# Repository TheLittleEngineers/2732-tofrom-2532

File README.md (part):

# 2732-tofrom-2532 - GCC-ECS-0001.1 - 2732/2532 E.P.R.O.M. Socket Converter

<!DOCTYPE html>
<html>
<head>

<meta name="Author" content="Robert &quot;The R.A.T.&quot; Allen Turner">
<meta name="GENERATOR" content="Tandy Radio Shack TRS-80 Color Computer 3">
<meta name="ProgId" content="TeleWriter-128.by.Bob.Van.der.Poel.for.Cognitec">
<meta http-equiv="Content-Type" content="text/html; charset=UTF-8">
<meta http-equiv="Content-Language" content="en-us">
<meta name="viewport" content="width=device-width, initial-scale=1">
<!--
<!meta http-equiv="Content-Type" content="text/html; charset=windows-1252">
This HTML is a veritable train wreck, however, it seems to get the job done on 24 September 2020 and beyond
-->

</head>

<body style="background-color:WhiteSmoke;">

<!-- Top Row -->
<div align="center">
  
<center>
  
<p align="center"><font size="6">

This page created: April 7, 2019, last updated: September 24, 2020.<br>
2732-tofrom-2532 - GCC-ECS-0001.1<br></font>
<font size="5"><em>2732/2532 E.P.R.O.M. Socket Converter</em><br></font><font size="4">A Project By <a href="http://www.TheLittleEngineers.org/" target="_blank">
The Little Engineers</a>.<br>Copyright &copy;2019, by:<br>
Robert "The R.A.T." Allen Turner<br>
<a href="http://www.TheLittleEngineers.org/" target="_blank">http://www.TheLittleEngineers.org/</a><br>
<a href="mailto:TheLittleEngineers@outlook.com">TheLittleEngineers@outlook.com</a><br>
<a href="mailto:OurLittleEngineers@gMail.com">OurLittleEngineers@gMail.com</a><br></div>
<div align="justify">
<p align="justify"><b>(Deprecated - See below for 
<a href="https://github.com/TheLittleEngineers/2732-to-2532" target="_blank">link</a> to the new version).</b>
</p>
This product is intended to allow a 2732 EPROM to be placed into a 2532 EPROM socket or a 2532 EPROM to be placed into a 2732 EPROM socket. The original product seems to have been placed on
<a href="https://github.com/TheLittleEngineers/" target="_blank">GitHub</a> at this url: 
<a href="https://github.com/ricardoquesada/2732-to-2532" target="_blank">https://github.com/ricardoquesada/2732-to-2532</a>. Being somewhat involved in the original creation of the product, I decided not to fork that repository for this new, slightly improved version, but rather chose to create a new repository. The product is now licensed under a 
<a href="https://creativecommons.org/licenses/by-sa/4.0/" target="_blank">Creative Commons Attribution-ShareAlike 4.0 International</a> (<a href="https://creativecommons.org/licenses/by-sa/4.0/legalcode" target="_blank">CC BY-SA 4.0</a>) License 
<i>IN MEMORY OF MY FATHER, ROBERT EMBRY TURNER</i>.</p>
<hr align="justify">
<p align="center">This version of the product has been shared to 
<a href="https://oshpark.com/shared_projects/nMURuBKv" target="_blank">OSHPark</a>: 
<a href="https://oshpark.com/shared_projects/nMURuBKv" target="_blank">https://oshpark.com/shared_projects/nMURuBKv</a>
<br>
&nbsp;</p>
<p align="center"><b>2732 <--> 2532 Adapter Board: GCC-ECS-0001.1,<br>2532 <===> 2732 Socket Converter,<br>Original Part Number: GCC-ECS-0001.0,<br>Copyright (C) 04 May 2010,<br<By: "Little" John Eric Turner and "Big" John Robert Turner,<br>All Rights Reserved.<br>
<a href="http://www.GIMEchip.com/" target="_blank">http://www.GIMEchip.com/</a><br>Updated Part Number: GCC-ECS-0001.1,<br>By: "Uncle" Robert "The R.A.T." Allen Turner at the behest of "Little" and "Big" John,<br>Copyright (C) 09 April 2019,<br>Released under a 
<a href="https://creativecommons.org/licenses/by-sa/4.0/" target="_blank">Creative Commons Attribution-ShareAlike 4.0 International</a> (<a href="https://creativecommons.org/licenses/by-sa/4.0/legalcode" target="_blank">CC BY-SA 4.0</a>) License<br>IN MEMORY OF MY FATHER: ROBERT EMBRY TURNER. I LOVE AND MISS YOU DADDY! REST IN PEACE.</b></p>
      <br<By: "Little" John Eric Turner and "Big" John Robert Turner,<br>
<hr align="justify">
<p align="justify">This product is intended to allow a 2732 EPROM to be placed into a 2532 EPROM socket or a 2532 EPROM to be placed into a 2732 EPROM socket. Fitting I.C. pins for IC1 and a socket for IC2 allows a 2732 to be plugged into a 2532 socket, whilst fitting I.C. pins for IC2 and a socket for IC1 allows a 2532 to be plugged into a 2732 socket. It is recommended that "round pin headers" be used for the I.C. pins as they will plug directly into standard I.C. sockets without stressing them which would result in potential damage to the socket. A low-profile ZIF (Zero Insertion Force) socket is ideal for use as the actual socket for this device if repeated E.P.R.O.M. insertion and removal is expected. Otherwise, a low profile D.I.P. (Dual Inline Pin) socket should be used. The 2732 has an output enable signal in addition to the chip enable signal. In most cases, the output enable signal can simply be connected to ground. However, it may sometimes be desirable to connect the ouput enable signal to the chip enable signal. Jumpers JP1 and JP2 allow these settings. If JP1 is fitted, then the ouput enable will be connected to the chip enable. If JP2 is fitted, then the ouput enable will be connected to GND. JP1 and JP2 should NEVER be fitted at the same time - one or the other, but not both. In most cases, fitting JP2 will suffice. All of 
<a href="http://www.GIMEchip.com/" target="_blank">GIMEchip.com</a>'s designs are created for the benefit of the vintage computing community as a whole. Although we copyright all of our works and retain all rights to them, we also don't mind sharing. If you wish to produce and distribute this product, please contact us at: 
<a href="mailto:sales@GIMEchip.com">sales@gimechip.com</a>. In most* cases, permissions will be granted Royalty Free. I said we like to share, didn't I? *As of 09 April 2019, it is no longer neccessary to request permissions to use this product. This is due to the release of Version 0001.0 and the NEW Version 0001.1 under a 
<a href="https://creativecommons.org/licenses/by-sa/4.0/" target="_blank">Creative Commons Attribution-ShareAlike 4.0 International</a> (<a href="https://creativecommons.org/licenses/by-sa/4.0/legalcode" target="_blank">CC BY-SA 4.0</a>) License. This allows for almost any use, including commercial.
If you would like to include this product as part of your website, feel free to do so, as long as all documentation remains intact. We do ask that you inform us that you have included this file on your site so our ego's may get a bit larger :-)** Enjoy - "Little" John Eric and "Big" John Robert Turner, Son and Father. **NOTE: Due to the new licensing (<a href="https://creativecommons.org/licenses/by-sa/4.0/legalcode" target="_blank">CC BY-SA 4.0</a>), it is now allowable to alter the documentation and there is no need to inform us of any website inclusion, however, attribution is still required (although we really won't complain if you forget.) THANK YOU! The Update to Version 0001.1 was done by: Robert Allen Turner, who acquired the
<a href="http://www.GIMEchip.com/" target="_blank">GIMEchip.com</a> domain name on 25 December 2018. Please note that Robert Allen Turner is unable to answer any inquiries in relation to 
<a href="http://www.GIMEchip.com/" target="_blank">GIMEchip.com</a> prior to his acquisition of same. Robert Allen Turner is in the process of releasing all prior 
<a href="http://www.GIMEchip.com/" target="_blank">GIMEchip.com</a> designs under the 
<a href="https://creativecommons.org/licenses/by-sa/4.0/legalcode" target="_blank">CC BY-SA 4.0</a> License. This is an ambitious undertaking which is likely to require a very large amount of time.</p>
<hr align="justify">
<p align="justify">Please note: This product is derived from an original design by "Little" John Eric and/or his father "Big" John Robert (J.R.) by "Uncle" Robert Allen. It should be thoroughly scrutinized and verified prior to actual use of any kind. 
&nbsp;</p>
<p align="center">
<b><em>
PLEASE NOTE: THIS VERSION HAS NOT YET BEEN TESTED.</em></b>
<br>
<b>This version is deprecated - please see the new version here: 
<a href="https://github.com/TheLittleEngineers/2732-to-2532" target="_blank">https://github.com/TheLittleEngineers/2732-to-2532</a></b></p>

<hr align="justify">

</font>
      <p align="justify"><font size="3">This repository and/or publication may contain one or more C.A.D. Libraries, such as for E.A.G.L.E., KiCAD, etcetera. You may use these libraries in your own projects,  however, please take note that we CANNOT guarantee the accuracy of the components (nor any part of these libraries and/or publications). We make NO guarantees that the components, footprints or schematic symbols contained in these libraries are flawless, and we make no promises of fitness for production, prototyping or any other purpose. These libraries and/or publications are provided for informational purposes only, and are used at your own discretion. By downloading these libraries 
      and/or publications, you agree that we cannot be held responsible for faulty PCBs (Printed Circuit Boards). <b>You should always check the footprints with a 1:1 printout.</b> Neither Robert Allen Turner, <a href="https://www.facebook.com/OurLittleEngineers/" target="_blank">The</a> <a href="https://www.facebook.com/groups/985537051651794/" target="_blank">Little</a> <a href="https://www.facebook.com/TheLittleEngineers.org" target="_blank">Engineers</a>, <a href="http://www.TheLittleEngineers.org/" target="_blank">TheLittleEngineers.org</a>, <a href="http://www.RoboCircuits.org/" target="_blank">RoboCircuits</a>, <a href="http://www.RoboCircuits.org/" target="_blank">RoboCircuits.org</a>, <a href="https://www.facebook.com/tincansandducttape/" target="_blank">Tin</a> <a href="https://www.facebook.com/groups/1654785514796788/" target="_blank">Cans</a> <a href="https://www.facebook.com/Tin-Cans-Duct-Tape-728969003939754/" target="_blank">And</a> <a href="https://www.facebook.com/groups/1828354620822631/" target="_blank">Duct</a> <a href="https://www.facebook.com/groups/228910954180459/" target="_blank">Tape</a>, <a href="http://www.tincansandducttape.com/" target="_blank">TinCansAndDuctTape.com</a>, <a href="http://www.tcadt.com/" target="_blank">TCADT</a>, <a href="http://www.tcadt.com/" target="_blank">TCADT.com</a>, <a href="http://www.CannedLogic.com/" target="_blank">Canned Logic</a>, <a href="http://www.CannedLogic.com/" target="_blank">CannedLogic.com</a>, <a href="http://www.RetroATX.com/" target="_blank">RetroATX</a>, <a href="http://www.RetroATX.com/" target="_blank">RetroATX.com</a>, <a href="http://www.Retro-ATX.com/" target="_blank">Retro-ATX</a>, <a href="http://www.Retro-ATX.com/" target="_blank">Retro-ATX.com</a>, <a href="http://www.TheLittleEngineers.org/pages/reference/20200112/ZombieSoftwareSystems" target="_blank">Zombie</a> <a href="http://www.TheLittleEngineers.org/pages/reference/20200112/ZombieSoftwareSystems" target="_blank">Software</a> <a href="http://www.TheLittleEngineers.org/pages/reference/20200112/ZombieSoftwareSystems" target="_blank">Systems</a>, <a href="http://www.TheLittleEngineers.org/pages/reference/20200112/BinarySystems" target="_blank">Binary</a> <a href="http://www.TheLittleEngineers.org/pages/reference/20200112/BinarySystems" target="_blank">Systems</a>, <a href="http://www.GIMEchip.com/" target="_blank">GIMEchip</a>, <a href="http://www.GIMEchip.com/" target="_blank">GIMEchip.com</a>, nor anyone affiliated with same shall be held responsible for any outcome resulting from the usage of these files. Should any errors be found, please contact us at one of the above email addresses and we will attempt to repair them. Unless otherwise noted, content of this library is licensed under a <a href="https://creativecommons.org/licenses/by-sa/4.0/" target="_blank">Creative Commons Attribution-ShareAlike 4.0 International</a> 
      <a href="%20https:/creativecommons.org/licenses/by-sa/4.0/legalcode" target="_blank">(CC BY-SA 4.0)</a> License on 04 Junel 2019 in memory of my Father, Robert Embry Turner, 1945-2019 - I LOVE AND MISS YOU DAD! Rest In Peace.
      </p>
     <hr align="justify">

<p align="center">
<font size="6"><a href="http://www.TheLittleEngineers.org/" target="_blank">The</a> <a href="http://www.TheLittleEngineers.org/" target="_blank">Little</a> <a href="http://www.TheLittleEngineers.org/" target="_blank">Engineers</a> in conjunction with <a href="http://www.RetroATX.com" target="_blank">Retro</a><u>-</u><a href="http://www.Retro-ATX.com" target="_blank">ATX</a><br></font>
<font size="5"><em><b><a href="https://www.facebook.com/OurLittleEngineers/" target="_blank">Pulling</a> <a href="https://www.facebook.com/groups/985537051651794/" target="_blank">The</a> <a href="https://www.facebook.com/groups/566741160795144/" target="_blank">Past</a> <a href="https://www.facebook.com/TheLittleEngineers.org" target="_blank">Into</a> <a href="https://www.facebook.com/tincansandducttape/" target="_blank">The</a> <a href="https://www.facebook.com/Tin-Cans-Duct-Tape-728969003939754/" target="_blank">Present</a> <a href="https://www.facebook.com/groups/1654785514796788/" target="_blank">For</a> <a href="https://www.facebook.com/groups/1828354620822631/" target="_blank">The</a> <a href="https://www.facebook.com/groups/1451396811790867/" target="_blank">Future</a></b></em><br></font>
</p>
<p align="justify"><a href="http://www.TheLittleEngineers.org/" target="_blank">The</a> <a href="http://www.TheLittleEngineers.org/" target="_blank">Little</a> <a href="http://www.TheLittleEngineers.org/" target="_blank">Engineers</a> is a project began in 2011 by <a href="mailto:TheLittleEngineers@OutLook.com" target="_blank">Robert</a> <a href="mailto:LittleEngineer_RAT@OutLook.com" target="_blank">Allen</a> <a href="mailto:OurLittleEngineers@gMail.com" target="_blank">Turner</a> (hereafter, <a href="mailto:LittleEngineer.RAT@gMail.com" target="_blank">I</a>, <a href="mailto:TinCansAndDuctTape@gMail.com" target="_blank">Me</a>, <a href="mailto:CannedLogic@gMail.com" target="_blank">My</a>, <a href="mailto:TinCansAndDuctTape@OutLook.com" target="_blank">Author</a>, or <a href="mailto:LittleEngineer.RAT@OutLook.com" target="_blank">&quot;The R.A.T.&quot;</a>), for the benefit of foster children and their families (foster and biological). The original intent was simply to provide a means, in the form of donated cameras, of creating videos with the foster families such that the biological parents did not completely miss out on their children growing up. Providing simple to construct kits (electronics, arts, crafts, etcetera) seemed a logical choice as subject matter for such videos and these types of activities have the benefit of being educational. It is thus that those types of projects are primarily what <a href="mailto:LittleEngineer.RAT@OutLook.com" target="_blank">I</a> attempt to develop for use in such videos. This is a difficult, time consuming and expensive undertaking. Each case must be handled on an individual basis and any such videos and communications must be scrutinized and approved on a per case basis by the case workers, et alia in charge. Although this makes such an undertaking extremely difficult, it is a necessity in order to protect the children. Some are, after all, being protected from abusive family members and so there has to be a very strict set of protocols in place. This has prevented me from fully launching <a href="https://www.facebook.com/OurLittleEngineers/" target="_blank">The</a> <a href="https://www.facebook.com/groups/985537051651794/" target="_blank">Little</a> <a href="https://www.facebook.com/TheLittleEngineers.org" target="_blank">Engineers</a> over the past eight years, but I remain fully committed to the project with the intent of seeing it through to a fully operational entity.
</p>
<p align="justify"><a href="http://www.RetroATX.com" target="_blank">Retro</a><u>-</u><a href="http://www.Retro-ATX.com" target="_blank">ATX</a> was conceived with the sole purpose of creating &quot;ATX form factor&quot; versions of various <em>classic</em> and <i>vintage</i> computing and other systems. Such a system might be an Altair 8800 &quot;clone&quot; in an ATX or &micro;ATX form factor. Certainly, a system compatible with the Tandy Radio Shack TRS-80 Model II, 12, 16 and 6000 line of computers is planned, as are ATX or &micro;ATX versions of the following systems:<ul align="justify"><li align="justify">Sinclair QL</li><li align="justify">Dragon D64 and D200</li><li align="justify">Dragon Alpha</li><li align="justify">Dragon Beta</li><li align="justify">Tandy Color Computer 3</li><li align="justify">Mattel Intellivision &quot;Keyboard Component&quot;</li><li align="justify">Aamber Pegasys</li><li align="justify">MicroBox ][</li><li align="justify">Various Frank Hogg Laboratories Systems, including:<ul align="justify"><li align="justify">FHL &quot;K-Buss&quot; backplanes of many sizes and configurations</li><li align="justify">FHL Tomcat Series, including:<ul align="justify"><li align="justify">FHL TC-9 6809 CPU board</li><li align="justify">FHL TC-9 I/O board</li><li align="justify">FHL TC-70 68070 CPU board</li><li align="justify">FHL TC-70 I/O and all other boards</li></ul></li></ul></li><li align="justify">GIMIX 6800/6809 Series Motherboards</li><li align="justify">GIMIX 6800/6809 Series CPU boards</li><li align="justify">GIMIX 6800/6809 Series Peripheral Cards</li><li align="justify">SWTPC 6800/6809 Series Motherboards</li><li align="justify">SWTPC 6800/6809 Series CPU boards</li><li align="justify">SWTPC 6800/6809 Series Peripheral Cards</li></ul>
</p>
<p align="justify">The above list represents just some of the systems that are planned for reimplementation by <a href="http://www.RetroATX.com" target="_blank">Retro</a><u>-</u><a href="http://www.Retro-ATX.com" target="_blank">ATX</a>. Any suggestions for other systems and features are welcomed. The MicroBox ][, Aamber Pegasus and Frank Hogg Laboratory systems are a priority at present, although this may change based upon feedback received. Undertaking any one of the above projects is a monumental task, requiring the expenditure of many hours of work and yet we fully intend to complete each and every one of those projects as time and resources allow. It is very unlikely that we will be able to complete all of these projects without the assistance of the many members of the <em>&quot;Vintage Computing Community&quot;.</em> We are in dire need of donations of any of the following items:<ul align="justify"><li align="justify">SCHEMATICS, documentations, Theory of Operations, etcetera of any and all of the above listed equipment</li><li align="justify">Any of the above hardware and peripherals that you may no longer have need of, functional or not</li><li align="justify">Your expertise, experience, opinions, engineering and other skills, etcetera</li></ul><b>Any items of interest, from the above list(s) or otherwise may be delivered to:</b>
</p>
<p align="center"><b>The Little Engineers Project/RetroATX.com<br>C/O Robert Turner<br>69 Lilly Lane<br>Pell City, AL 35125<br><a href="mailto:OurLittleEngineers@gMail.com?subject=Donations">OurLittleEngineers@gMail.com</a></b></p>
<p align="justify">Your continued encouragement and <a href="#support">support</a> are greatly appreciated. Other methods of <a href="#digitalcurrency">potential</a> <a href="#patreon">support</a> are contained <a href="#support">further</a> into this <a href="#support">document</a>. Thank You and God Bless.</p>
 
<p align="justify"><b>The logos, names and other material relating to <a href="https://www.facebook.com/OurLittleEngineers/" target="_blank">The</a> <a href="https://www.facebook.com/groups/985537051651794/" target="_blank">Little</a> <a href="https://www.facebook.com/TheLittleEngineers.org" target="_blank">Engineers</a>, <a href="http://www.TheLittleEngineers.org/" target="_blank">TheLittleEngineers.org</a>, <a href="http://www.RoboCircuits.org/" target="_blank">RoboCircuits</a>, <a href="http://www.RoboCircuits.org/" target="_blank">RoboCircuits.org</a>, <a href="https://www.facebook.com/tincansandducttape/" target="_blank">Tin</a> <a href="https://www.facebook.com/groups/1654785514796788/" target="_blank">Cans</a> <a href="https://www.facebook.com/Tin-Cans-Duct-Tape-728969003939754/" target="_blank">And</a> <a href="https://www.facebook.com/groups/1828354620822631/" target="_blank">Duct</a> <a href="https://www.facebook.com/groups/228910954180459/" target="_blank">Tape</a>, <a href="http://www.tincansandducttape.com/" target="_blank">TinCansAndDuctTape.com</a>, <a href="http://www.tcadt.com/" target="_blank">TCADT</a>, <a href="http://www.tcadt.com/" target="_blank">TCADT.com</a>, <a href="http://www.CannedLogic.com/" target="_blank">Canned Logic</a>, <a href="http://www.CannedLogic.com/" target="_blank">CannedLogic.com</a>, <a href="http://www.RetroATX.com/" target="_blank">RetroATX</a>, <a href="http://www.RetroATX.com/" target="_blank">RetroATX.com</a>, <a href="http://www.Retro-ATX.com/" target="_blank">Retro-ATX</a>, <a href="http://www.Retro-ATX.com/" target="_blank">Retro-ATX.com</a>, <a href="http://www.TheLittleEngineers.org/pages/reference/20200112/ZombieSoftwareSystems" target="_blank">Zombie</a> <a href="http://www.TheLittleEngineers.org/pages/reference/20200112/ZombieSoftwareSystems" target="_blank">Software</a> <a href="http://www.TheLittleEngineers.org/pages/reference/20200112/ZombieSoftwareSystems" target="_blank">Systems</a>, <a href="http://www.TheLittleEngineers.org/pages/reference/20200112/BinarySystems" target="_blank">Binary</a> <a href="http://www.TheLittleEngineers.org/pages/reference/20200112/BinarySystems" target="_blank">Systems</a>, <a href="http://www.GIMEchip.com/" target="_blank">GIMEchip</a> and <a href="http://www.GIMEchip.com/" target="_blank">GIMEchip.com</a> are the sole property of <a href="https://www.facebook.com/TheLittleEngineers.org" target="_blank">Robert</a> <a href="mailto:TheLittleEngineers@OutLook.com" target="_blank">Allen</a> <a href="https://www.facebook.com/TinCansDuctTape" target="_blank">Turner</a> with <em>All Rights Reserved</em>.</b> The rights to the <a href="http://www.GIMEchip.com/" target="_blank">GIMEchip.com</a> domain and <a href="https://www.github.com/TheLittleEngineers?tab=repositories" target="_blank">products</a> were acquired by the <a href="https://www.facebook.com/TheLittleEngineers.org" target="_blank">author</a> on 25 December 2018 from my brother and his son, the former owners/operators of <a href="http://www.GIMEchip.com/" target="_blank">GIMEchip.com</a>. Please note that the author is unable to answer any inquiries, including those of support or otherwise, in relation to <a href="http://www.GIMEchip.com/" target="_blank">GIMEchip.com</a> prior to his acquisition of same on 25 December 2018. This is primarily because the author posseses no knowlege of the site operation prior to that time. Although I have been provided with a large number of files that were originally contained on the website, it is unlikely that I will resurrect <a href="http://www.GIMEchip.com/" target="_blank">GIMEchip.com</a> other than perhaps as a <a href="http://www.TheLittleEngineers.org/WebSites/GIMEchip/" target="_blank">page</a> on <a href="http://www.TheLittleEngineers.org/WebSites/GIMEchip/" target="_blank">one</a> of my other websites. These files are mostly HTML page files and C.A.D. files of the products designed and developed by my nephew and his father, and very little else. As part of the acquisition agreement, all products previously produced by <a href="http://www.GIMEchip.com/" target="_blank">GIMEchip.com</a> are to be released under a <a href="http://www.TheLittleEngineers.org/pages/reference/20200112/CreativeCommons/CCBYSA.htm" target="_blank">Creative Commons Attribution-ShareAlike 4.0 International</a> <a href="http://www.TheLittleEngineers.org/pages/reference/20200112/CreativeCommons/CCBYSALegalCode.htm" target="_blank">(CC BY-SA 4.0)</a> License, as time and resources permit. Although many of these projects are somewhat interesting, none of them seem particularly useful or revolutionary.</p>
<p align="center">
<font size="6">DISCLAIMER:<br></font>
<font size="5"><em>Please Read Carefully.<br></em></font>
</p>
<p align="justify">This information is provided for informational purposes only. Any attempt to modify your equipment (including, but not limited to kit assembly) without the proper skills to do so may void your equipment. Any attempt to modify your equipment without unplugging it first may void you. This Information is provided "as-is" with no guarantee of fitness for any purpose, either explicit or implied. We disclaim any and all responsibility for losses incurred through the use of this information. Included with this information may be one or more C.A.D. Libraries, such as for E.A.G.L.E., KiCAD, etcetera. Any such C.A.D. libraries, except as may be noted are released under a <a href="http://www.TheLittleEngineers.org/pages/reference/20200112/CreativeCommons/CCBYSA.htm" target="_blank">Creative Commons Attribution-ShareAlike 4.0 International</a> <a href="http://www.TheLittleEngineers.org/pages/reference/20200112/CreativeCommons/CCBYSALegalCode.htm" target="_blank">(CC BY-SA 4.0)</a> License. You may use these libraries in your own projects, however, please take note that we CANNOT guarantee the accuracy of the components (nor any part of these libraries and/or information). We make NO guarantees that the components, footprints or schematic symbols contained in these libraries are flawless, and we make no promises of fitness for production, prototyping or any other purpose. These libraries and/or information are provided for informational purposes only, and are used at your own discretion. By downloading these libraries and/or information, you agree that we cannot be held responsible for faulty PCBs (Printed Circuit Boards). <b>You should always check the footprints with a 1:1 printout.</b> Neither Robert Allen Turner, <a href="https://www.facebook.com/OurLittleEngineers/" target="_blank">The</a> <a href="https://www.facebook.com/groups/985537051651794/" target="_blank">Little</a> <a href="https://www.facebook.com/TheLittleEngineers.org" target="_blank">Engineers</a>, <a href="http://www.TheLittleEngineers.org/" target="_blank">TheLittleEngineers.org</a>, <a href="https://www.facebook.com/tincansandducttape/" target="_blank">Tin</a> <a href="https://www.facebook.com/groups/1654785514796788/" target="_blank">Cans</a> <a href="https://www.facebook.com/Tin-Cans-Duct-Tape-728969003939754/" target="_blank">And</a> <a href="https://www.facebook.com/groups/1828354620822631/" target="_blank">Duct</a> <a href="https://www.facebook.com/groups/228910954180459/" target="_blank">Tape</a>, <a href="http://www.tincansandducttape.com/" target="_blank">TinCansAndDuctTape.com</a>, <a href="http://www.tcadt.com/" target="_blank">TCADT</a>, <a href="http://www.tcadt.com/" target="_blank">TCADT.com</a>, <a href="http://www.CannedLogic.com/" target="_blank">Canned Logic</a>, <a href="http://www.CannedLogic.com/" target="_blank">CannedLogic.com</a>, <a href="http://www.RetroATX.com/" target="_blank">RetroATX</a>, <a href="http://www.RetroATX.com/" target="_blank">RetroATX.com</a>, <a href="http://www.Retro-ATX.com/" target="_blank">Retro-ATX</a>, <a href="http://www.Retro-ATX.com/" target="_blank">Retro-ATX.com</a>, <a href="http://www.RoboCircuits.org/" target="_blank">RoboCircuits</a>, <a href="http://www.RoboCircuits.org/" target="_blank">RoboCircuits.org</a>, <a href="http://www.TheLittleEngineers.org/pages/reference/20200112/ZombieSoftwareSystems" target="_blank">Zombie</a> <a href="http://www.TheLittleEngineers.org/pages/reference/20200112/ZombieSoftwareSystems" target="_blank">Software</a> <a href="http://www.TheLittleEngineers.org/pages/reference/20200112/ZombieSoftwareSystems" target="_blank">Systems</a>, <a href="http://www.TheLittleEngineers.org/pages/reference/20200112/BinarySystems" target="_blank">Binary</a> <a href="http://www.TheLittleEngineers.org/pages/reference/20200112/BinarySystems" target="_blank">Systems</a>, <a href="http://www.GIMEchip.com/" target="_blank">GIMEchip</a>, <a href="http://www.GIMEchip.com/" target="_blank">GIMEchip.com</a>, nor anyone affiliated with same shall be held responsible for any outcome resulting from the usage of these files and/or information. Should any errors be found, please contact us at one of the provided email addresses and we will attempt to repair them. Unless otherwise noted, content of this library and other information is licensed under a <a href="http://www.TheLittleEngineers.org/pages/reference/20200112/CreativeCommons/CCBYSA.htm" target="_blank">Creative Commons Attribution-ShareAlike 4.0 International</a> <a href="http://www.TheLittleEngineers.org/pages/reference/20200112/CreativeCommons/CCBYSALegalCode.htm" target="_blank">(CC BY-SA 4.0)</a> License, <b><em>in memory of my Father</em>, <i>Robert Embry Turner</i>, 1945-2019 - I LOVE AND MISS YOU DAD! <em>Rest In Peace</em></b>. By using this information, you are deemed to have accepted these terms and conditions of use, and you agree NOT to sue us.</p>
<p align="center"><font size="5"><em>CLARIFICATION:</em></font></p>
<p align="justify">The disclaimer states as plainly as possible that if you decide to make use of any of the information contained within this document and/or any of the accompanying files that you do so at your own risk. Designing products for the <a href="http://www.TheLittleEngineers.org/" target="_blank">Little Engineers Project</a> and/or affiliates is not motivated by any desire of profits. As this is a not for profit venture, obviously we can't afford not to disclaim the use of this information. Thank You for your understanding and acceptance of these terms of use.</p>
<hr>
<!-- /Top Row -->

<!-- Top Left Column -->
<div class="row" style="background-color:WhiteSmoke;" align="center">
<div class="column" style="background-color:WhiteSmoke;" align="center">
<h2 align="center"><a href="http://www.TheLittleEngineers.org/pages/reference/20200103/IMDb/WhoAmI.htm" target="_blank">Who Am I?</a><br>Hint: I'm Not <a href="http://www.TheLittleEngineers.org/pages/reference/20200103/IMDb/JackieChan.htm" target="_blank">Jackie Chan</a>.<br>I Did Enjoy That Film Immensely.</h2>
<p align="justify">The headline of this paragraph is merely an attempt at humor while allowing me the opportunity to mention a <a href="http://www.TheLittleEngineers.org/pages/reference/20200103/IMDb/WhoAmI.htm" target="_blank">film</a> that my son and I quite thoroughly enjoyed when it was released during his childhood in 1998, leading to his eventual love of <a href="http://www.TheLittleEngineers.org/pages/reference/20200112/IMDb/JackieChanAdventures.htm" target="_blank">&quot;The Jackie Chan Adventures&quot;</a> animated series, which would be released some two years later in 2000. Most of the world seemed to be concerned with the overhyped <a href="http://www.TheLittleEngineers.org/pages/reference/20200112/Y2K/Y2KBug.htm" target="_blank">&quot;Y2K Bug&quot;</a> and we were just watching <a href="http://www.TheLittleEngineers.org/pages/reference/20200103/IMDb/JackieChan.htm" target="_blank">Jackie</a> <a href="http://www.TheLittleEngineers.org/pages/reference/20200112/IMDb/JackieChanAdventures.htm" target="_blank">Chan</a> and enjoying our lives while playing <a href="http://www.TheLittleEngineers.org/pages/reference/20200112/NickMarentes/CosmicAmbush.htm" target="_blank">&quot;Cosmic Ambush&quot;</a> and <a href="http://www.TheLittleEngineers.org/pages/reference/20200112/GoSub/TheCrystalCityGitHub.htm" target="_blank">&quot;</a><a href="http://www.TheLittleEngineers.org/pages/reference/20200112/GoSub/GoSubZenixTheCrystalCity.htm" target="_blank">The</a> <a href="http://www.TheLittleEngineers.org/pages/reference/20200112/GoSub/JeremySpillerResume.htm" target="_blank">Crystal</a> <a href="http://www.TheLittleEngineers.org/pages/reference/20200112/GoSub/SixtyFramesPerSecondOrBust.htm" target="_blank">City</a><a href="http://www.TheLittleEngineers.org/pages/reference/20200112/GoSub/TheCrystalCityGitHub.htm" target="_blank">&quot;</a> on our 512K CoCo 3. The following text serves as a general Introduction to <a href="mailto:TheLittleEngineers@OutLook.com" target="_blank">Robert</a> <a href="mailto:LittleEngineer_RAT@OutLook.com" target="_blank">&quot;The R.A.T.&quot;</a> <a href="mailto:OurLittleEngineers@gMail.com" target="_blank">Allen</a> <a href="mailto:LittleEngineer.RAT@gMail.com" target="_blank">Turner</a>, <a href="http://www.TheLittleEngineers.org/pages/reference/20200112/ZombieSoftwareSystems" target="_blank">Zombie</a> <a href="http://www.TheLittleEngineers.org/pages/reference/20200112/ZombieSoftwareSystems" target="_blank">Software</a> <a href="http://www.TheLittleEngineers.org/pages/reference/20200112/ZombieSoftwareSystems" target="_blank">Systems</a>, <a href="http://www.TheLittleEngineers.org/pages/reference/20200112/BinarySystems" target="_blank">Binary</a> <a href="http://www.TheLittleEngineers.org/pages/reference/20200112/BinarySystems" target="_blank">Systems</a>, <a href="https://www.facebook.com/OurLittleEngineers/" target="_blank">The</a> <a href="https://www.facebook.com/groups/985537051651794/" target="_blank">Little</a> <a href="https://www.facebook.com/TheLittleEngineers.org" target="_blank">Engineers</a>, <a href="http://www.TheLittleEngineers.org/" target="_blank">TheLittleEngineers.org</a>, <a href="https://www.facebook.com/tincansandducttape/" target="_blank">Tin</a> <a href="https://www.facebook.com/groups/1654785514796788/" target="_blank">Cans</a> <a href="https://www.facebook.com/Tin-Cans-Duct-Tape-728969003939754/" target="_blank">And</a> <a href="https://www.facebook.com/groups/1828354620822631/" target="_blank">Duct</a> <a href="https://www.facebook.com/groups/228910954180459/" target="_blank">Tape</a>, <a href="http://www.tincansandducttape.com/" target="_blank">TinCansAndDuctTape.com</a>, <a href="http://www.tcadt.com/" target="_blank">TCADT</a>, <a href="http://www.tcadt.com/" target="_blank">TCADT.com</a>, <a href="http://www.CannedLogic.com/" target="_blank">Canned Logic</a>, <a href="http://www.CannedLogic.com/" target="_blank">CannedLogic.com</a>, <a href="http://www.RetroATX.com/" target="_blank">RetroATX</a>, <a href="http://www.RetroATX.com/" target="_blank">RetroATX.com</a>, <a href="http://www.Retro-ATX.com/" target="_blank">Retro-ATX</a>, <a href="http://www.Retro-ATX.com/" target="_blank">Retro-ATX.com</a>, <a href="http://www.RoboCircuits.org/" target="_blank">RoboCircuits</a>, <a href="http://www.RoboCircuits.org/" target="_blank">RoboCircuits.org</a>, <a href="http://www.GIMEchip.com/" target="_blank">GIMEchip</a> and <a href="http://www.GIMEchip.com/" target="_blank">GIMEchip.com</a>. Please note that the <a href="http://www.GIMEchip.com/" target="_blank">GIMEchip.com</a> domain was acquired by <a href="mailto:TheLittleEngineers@OutLook.com" target="_blank">Robert</a> <a href="mailto:LittleEngineer_RAT@OutLook.com" target="_blank">&quot;The R.A.T.&quot;</a> <a href="mailto:OurLittleEngineers@gMail.com" target="_blank">Allen</a> <a href="mailto:LittleEngineer.RAT@gMail.com" target="_blank">Turner</a> on December 25, 2018 from the prior owners, who happen to be his brother (J.R. a.k.a. John Robert a.k.a. &quot;Big John&quot;) and nephew (J.E. a.k.a. John Eric a.k.a. &quot;Little John&quot;). As such, <a href="mailto:LittleEngineer.RAT@OutLook.com" target="_blank">&quot;The R.A.T.&quot;</a> is unable to answer any inquiries regarding any products or services of <a href="http://www.GIMEchip.com/" target="_blank">GIMEchip.com</a> prior to that date simply because I have no knowledge of the site. I have attempted to utilize the <a href="http://www.TheLittleEngineers.org/pages/reference/20200103/GIMEchip/GIMEchipWayBackMachine.htm" target="_blank">Internet Archive WayBack Machine</a> to have a look at the <a href="http://www.TheLittleEngineers.org/pages/reference/20200103/GIMEchip/GIMEchipWayBackMachine.htm" target="_blank">site</a> at various stages of existence, but there seems to be very little there as of the date of this writing (April 10, 2019). <a href="mailto:LittleEngineer_RAT@OutLook.com" target="_blank">&quot;The R.A.T.&quot;</a> has also acquired the rights to all products previously produced by <a href="http://www.GIMEchip.com/" target="_blank">GIMEchip.com</a> and its previous owners. As part of the acquisition agreement, all of those products will be released as open source, under a <a href="http://www.TheLittleEngineers.org/pages/reference/20200112/CreativeCommons/CCBYSA.htm" target="_blank">Creative Commons Attribution-ShareAlike 4.0 International</a> <a href="http://www.TheLittleEngineers.org/pages/reference/20200112/CreativeCommons/CCBYSALegalCode.htm" target="_blank">(CC BY-SA 4.0)</a> License, as time and resources permit. Note that some of these products were previously released by my brother under an <a href="http://www.TheLittleEngineers.org/pages/reference/20200112/CreativeCommons/OSHWA.htm" target="_blank">Open Source Hardware License</a> and all of those releases remain available under that license. Making certain that any given product meets all of the requirements necessary for the <a href="http://www.TheLittleEngineers.org/pages/reference/20200112/CreativeCommons/OSHWA.htm" target="_blank">OSHWA</a> license is a time consuming task when preparing older archives for release and so I have decided to utilize a <a href="http://www.TheLittleEngineers.org/pages/reference/20200112/CreativeCommons/CCBYSA.htm" target="_blank">Creative Commons Attribution-ShareAlike 4.0 International</a> <a href="http://www.TheLittleEngineers.org/pages/reference/20200112/CreativeCommons/CCBYSALegalCode.htm" target="_blank">(CC BY-SA 4.0)</a> License for any releases prepared by myself. This should allow you to utilize the releases in almost any desired manner, including commercial, within the terms of the license.</p>
<h3 align="center">Introducing <a href="mailto:TheLittleEngineers@OutLook.com" target="_blank">T</a><a href="mailto:LittleEngineer_RAT@OutLook.com" target="_blank">h</a><a href="mailto:OurLittleEngineers@gMail.com" target="_blank">e</a> <a href="mailto:LittleEngineer.RAT@gMail.com" target="_blank">&quot;</a><a href="mailto:TinCansAndDuctTape@gMail.com" target="_blank">R</a><a href="mailto:CannedLogic@gMail.com" target="_blank">.</a><a href="mailto:TinCansAndDuctTape@OutLook.com" target="_blank">A</a><a href="mailto:LittleEngineer.RAT@OutLook.com" target="_blank">.</a><a href="mailto:TheLittleEngineers@OutLook.com" target="_blank">T</a><a href="mailto:LittleEngineer_RAT@OutLook.com" target="_blank">.</a><a href="mailto:OurLittleEngineers@gMail.com" target="_blank">&quot;</a></h3>
<p align="justify">I have started writing this introduction numerous times only to get sidetracked and derailed. Hopefully, I will be able to properly introduce myself this time. I will begin at the acquisition of my first personal computer, a Sinclair ZX81 Issue 3, produced by Timex and sold as the TS1000 (Timex Sinclair 1000 or T/S1000). This would be March 30, 1982 - My fourteenth birthday. My parents presented me with a Timex Sinclair 1000 (TS1000) computer, after much begging and pleading. The TS1000 is a ZX81 with a few differences: 2K of RAM, an [ENTER] key instead of [NEW LINE] or [N/L] and Timex branding. I had wanted a computer for so long, and Sir Clive Sinclair succeeded in making it affordable. Timex made it even more affordable as the TS1000 was placed on sale for $59.99 at the local "Big B" drug store, at the time, a division of Brunos Corporation (Food World, Food Fair, Consumer Warehouse, etcetera). I was ecstatic - I finally had a computer, and as limited as it was, I still mamaged to learn a great deal from that machine. This experience with the ZX81 (T/S1000) led to the creation of Zombie Software Systems, my first computer venture. When Timex announced the Timex Sinclair 2068 (TS2068) after canceling the TS2000 (a 48K Spectrum clone), I knew that I wanted it to be my next computer and my parents agreed to buy it for me for Christmas of 1983. Then, it happened: I walked into the local franchised Radio Shack store, operated at the time by Cisco Auto Parts, and there, on display right next to the entrance, was the newly introduced Color Computer 2 with 16K of RAM and Extended Color BASIC. It took mere moments for me to fall in love with that machine and I asked my parents for the Color Computer 2 instead of the TS2068. They placed it on lay-a-way as Christmas approached. It was eventually paid off and sat under the Christmas tree until Christmas Evening of 1983. They allowed me to open it on Christmas Evening and I was up all night working through the programs in the manuals. It was wonderful. This led to the creation of Binary Systems, my second computer venture. Eventually, I came across an advertisement in Radio-Electronics from a company by the name of Unicorn Electronics (a company that remains in business until this very day). They had a set of 4164 Dynamic RAM chips with a 150nS access time for, I think $9.95 (although I seem to remember $1.50 each, so perhaps it was $1.50 per chip or 8/$9.95). The chips were used but tested pulls. I ordered them, along with a bag of keyboard switches (intended to be used for building a better keyboard for my TS1000 and adding four function keys to the CoCo 2). When they arrived, I opened the case of my Color Computer 2, installed the 64K chips, soldered in the <b>W1</b> <em>jumper</em> and voila - I had a 64K ECB Color Computer 2. Although other systems of the time had better graphics and sound, the Color Computer line of systems by Radio Shack, a division of Tandy Corporation, would become (and remain) my favorite computers of all time. In fact, I still use them to this very day, having kept one Color Computer 3 (CoCo 3) when I passed my vintage computing collection to my brother, J.R. (John Robert) who then passed it on to his son, &quot;Little John&quot; (John Eric), but I will get to that after a brief reminiscence of ZSS and BS, as follows:</p>
<h3 align="center">ZSS or Zombie Software Systems:</h3>
<p align="justify">Zombie Software Systems was formed on my fourteenth birthday, 30 March 1982, as a sole proprietorship supporting the Timex and Sinclair computer systems.</p>
<h3 align="center">Supported systems initially included:</h3>
<p align="justify"><ul align="justify">
<li align="justify">Sinclair ZX80</li>
<li align="justify">Sinclair ZX81</li>
<li align="justify">Timex Sinclair 1000</li>
</ul>
<h3 align="center">Support was eventually added for:</h3>
<ul align="justify">
<li align="justify">Timex Sinclair 1500</li>
<li align="justify">The PC-8300 "Your Computer"</li>
<li align="justify">Sinclair Spectrum (All Versions)</li>
<li align="justify">Timex Sinclair 2068</li>
<li align="justify">Sinclair QL</li>
</ul>
<p align="justify">By 1991, and in conjunction with Binary Systems, support had been added for machines from Mattel, Atari, Tomy, Texas Instruments, Tandy Radio Shack, Commodore and many others.</p>
<h3 align="center">BS or Binary Systems:</h3>
<p align="justify">Binary Systems was formed on 23 December 1983, as a sole proprietorship supporting the Tandy Radio Shack computer systems.
<h3 align="center">Supported systems initially included:</h3>
<ul align="justify">
<li align="justify">TRS-80 Color Computer (CoCo 1)</li>
<li align="justify">Tandy Data Products TDP-100</li>
<li align="justify">TRS-80 Color Computer 2 (CoCo 2)</li>
<li align="justify">Dragon Data Dragon 32</li>
<li align="justify">Tano Dragon 64</li>
<li align="justify">TRS-80 Model I</li>
</ul>
</div>
<!-- /Top Left Column -->

<!-- Top Right Column -->
<div class="column" style="background-color:WhiteSmoke;" align="center">
<h3 align="center">Support was eventually added for:</h3>
<ul align="justify">
<li align="justify">TRS-80 Model III</li>
<li align="justify">TRS-80 Model IV</li>
<li align="justify">TRS-80 Model 4/4P</li>
<li align="justify">Tandy Color Computer 3</li>
</ul>
<p align="justify">By 1991, and in conjunction with Zombie Software Systems, support had been added for machines from Mattel, Atari, Tomy, Texas Instruments, Sinclair, Commodore, Amstrad, Kaypro and many others. The operation of Zombie Software Systems and Binary Systems was a labor of love more than anything else, as it never made a profit, but it was fun and remains among the best memories of my youth and early adulthood and I am thankful that the stroke
(see below) did not take these memories from me.</p>
<p align="justify">I continued to support these vintage machines until 2007 when I suffered a stroke. At that point, I passed operations on to my son, John (he and his cousin share both
the same name and same date of birth through a very odd coincidence). My son eventually made a mess of things and finally moved on to other hobbies. A side effect of the stroke was that I lost almost all interest in
computers and electronics, vintage and otherwise. It was thus that I presented my entire collection of vintage computers and electronics to my brother J.R. (John Robert or &quot;Big John&quot;). He took the opportunity to bond
with his son, J.E. (John Eric or &quot;Little John&quot;). &quot;Little John&quot; was facing a number of health issues, but he jumped in with both feet, teaching himself all about the Color Computer and other systems. He began to develop
a plethora of hardware projects for the Color Computer and other vintage systems. The earliest of his designs were rubbish due to his lack of skill, but he appears to have learned rather quickly, producing some amazing
designs. I have taken it upon myself to "redo" his earliest works, hopefully producing manufacturable products from them. The first of his designs to receive the "redesign" treatment from me is the &quot;FlexiMIDI&quot;, &quot;FlexiROM&quot;
and &quot;FlexiBuffer&quot; projects. Those three designs were excellent in concept, but rubbish in practice due to his lack of circuit design skills at the time that he developed them. They are certainly worth the time and effort
to redesign. He would eventually become disillusioned and abandon the hobby altogether. This was, in no small part, due to hackers repeatedly taking down his website: <a href="http://www.GIMEchip.com/" target="_blank">GIMEchip.com</a>. They (the unknown hackers) eventually
compromised his eBay and PayPal accounts, rendering them completely useless. That was the straw that broke the camels back, so to speak. He (&quot;Little John&quot;) gave up and moved to Tennessee. He left everything with his
father, my brother, and asked that his father release all of his works as open source. J.R. made several valiant efforts to honor that request, but never fully succeeded in releasing all of the works of &quot;Little John&quot;.
Fast Forward almost a decade...</p>

<h3 align="center">The Beginning of a Family Tragedy:</h3>
<p align="justify">November of 2018, my father, Robert Embry Turner fell ill and was hospitalized. As Christmas approached, he remained in the hospital. Many family members visited and it came to pass that I reconnected with J.R. and &quot;Little John&quot;. They asked me if I would like to have my old vintage computing collection back. At first, I was hesitant and uninterested. As my fathers condition worsened, I began to remember how hard my father worked to buy me those first computers. Tons of memories, good and bad, began to flood my mind. I decided to accept their offer. In addition to the hardware and software, they presented me with the <a href="http://www.GIMEchip.com/" target="_blank">GIMEchip.com</a> domain name. This became my Christmas present from my brother and his son. &quot;Little John&quot; asked that I finish what his father started: the release of all of  &quot;Little John's&quot; work as open source. I reluctantly agreed, though I was unsure if I could ever manage the time and effort to do so. I honestly was not prepared to take on such a monumental task. Then, tragedy struck.
<br><br>
On the day of January 4, 2019, my father died as I held his hand in that hospital room. His death had quite a profound effect on me. I almost lost my job while trying to come to terms with never being able to speak to my father again. I eventually began to recover, to an extent, but I began to think of everything and everyone that I had lost over the years. For one thing, my own son, also named John Eric Turner, and I are estranged. We "speak" online, but I have not seen him in a very long time<a href="#son">*</a>. He was unable to be at the hospital and did not get to say goodbye to my father before he died. As mentioned, my son and his cousin are both named John Eric Turner, and there is a story behind it, however, for the moment, suffice it to say that they both were named In Memory of Jon-Erik Hexum, who died on the set of "Cover Up" on Friday, October 12, 1984. As my mind wandered, I thought of my mother in law, Sarah Ann Channell, who passed away on January 12, 2003 and my father in law, Frank Leon Channell, who passed away on August 23, 2003. Even though I was divorced from their daughter, they were still family and their deaths were very painful to me and my son. Indeed, their deaths affected my son in such a way that he never fully recovered and that is partially what eventually led to our falling out in 2007 or 2008 and the resulting estrangement. I am sure that my addled state after that stroke also played a hand in the troubles between my son and I because I became very difficult to be around. Thinking about Sarah and Frank caused me to really begin missing my son and, even more, my father. I then thought about my best friend from high school, David Ray Poe, who died on May 20, 2013. Eight days prior to his death, he had sent me an email that I did not see until after he died. That email was a single sentence: "Did you die?". You can perhaps imagine the effect that reading the message had on me. In reality, he would often send a message like that when he had not heard from me in a while. Another close friend from high school, Steve Allen Cox, died on September 6, 2016. As all of the thoughts of everything and everyone that I had lost flooded my mind, I began to spiral and was in peril of losing myself. I needed a distraction, something to keep my mind occupied and perhaps aid in my coming to terms with the death of my father. I found that distraction in the form of that vintage computing collection and the projects that &quot;Little John&quot; had created. It is for that reason alone that you are now reading this and seeing those products, which I have decided to release under a <a href="http://www.TheLittleEngineers.org/pages/reference/20200112/CreativeCommons/CCBYSA.htm" target="_blank">Creative Commons Attribution-ShareAlike 4.0 International</a> <a href="http://www.TheLittleEngineers.org/pages/reference/20200112/CreativeCommons/CCBYSALegalCode.htm" target="_blank">(CC BY-SA 4.0)</a> License. What this means is that you, or anyone else for that matter, may use the products in almost any way that you may desire, even commercially. I am doing all of this to honor the memory of my father, Robert Embry Turner, and everyone else that I have lost. I truly hope that these products provide much enjoyment to all who discover them. I should point out that I have absolutely no desire to revive the <a href="http://www.GIMEchip.com/" target="_blank">GIMEchip.com</a> website, primarily because I do not have all of the files necessary to recreate <a href="http://www.GIMEchip.com/" target="_blank">GIMEchip.com</a>. It is very likely that I will stumble across some or all of the <a href="http://www.GIMEchip.com/" target="_blank">GIMEchip.com</a> website files as I begin to inventory everything that was included with my 2018 Christmas gift from &quot;Big and Little John&quot;. I also DO NOT wish to invoke the ire of those hackers who targeted my nephew and destroyed his website, eBay and PayPal accounts. I will very likely, however, forward the <a href="http://www.GIMEchip.com/" target="_blank">GIMEchip.com</a> domain to a page on my <a href="http://www.TheLittleEngineers.org/" target="_blank">http://www.TheLittleEngineers.org/</a> website or perhaps I will forward it to the GitHub page - I am currently undecided.

So, there you have it - most of what I wanted to say about how I came to posses all of the works of my nephew and his father, as well as their domain name, <a href="http://www.GIMEchip.com/" target="_blank">GIMEchip.com</a>. In addition to releasing all of their products under a <a href="http://www.TheLittleEngineers.org/pages/reference/20200112/CreativeCommons/CCBYSA.htm" target="_blank">Creative Commons Attribution-ShareAlike 4.0 International</a> <a href="http://www.TheLittleEngineers.org/pages/reference/20200112/CreativeCommons/CCBYSALegalCode.htm" target="_blank">(CC BY-SA 4.0)</a> License, I will also be releasing all of the Zombie Software Systems and Binary Systems products under identical licensing terms.</p>
  </div>
  </div>
  <hr>
<!-- /Top Right Column -->
 
<!-- Center Row -->
<p align="center">
<font size="6">Is ALL of this really FREE?<br></font>
<font size="5"><em>YES!</em></font>
</p>
<p align="justify" id="support">
Everything contained in the GitHub Repositories for these projects is free to use, even commercially, in accordance with the terms of the <a href="http://www.TheLittleEngineers.org/pages/reference/20200112/CreativeCommons/CCBYSA.htm" target="_blank">Creative Commons Attribution-ShareAlike 4.0 International</a> <a href="http://www.TheLittleEngineers.org/pages/reference/20200112/CreativeCommons/CCBYSALegalCode.htm" target="_blank">(CC BY-SA 4.0)</a>License. The Amazon Kindle and Paperback Publications, however, are not licensed for redistribution and are only available to our Patrons as a free ".PDF" or for purchase from Amazon. These particular publications help to generate revenue that is used for further developmental efforts. It is not necessary to purchase these publications in order to make use of the GitHub Repositories, however, such purchases provide the funds necessary for the development of future products. The repositories contain all necessary information needed to construct, assemble and use the products described therein. If you would like to support our continued developmental efforts, the remaining paragraphs detail several methods that may be used to offer support of our work.

As stated, I have absolutely no intention of charging any fees whatsoever in regards to the use of these products. Anyone who so desires may manufacture and sell any of these products, though they must state specifically that they will be providing any and all support as may be required. However, If you would care to support my work, donations are happily accepted, whether they be in the form of funds, vintage computing equipment, tools, components, etcetera. I am always in need of such items. I specifically need PAL versions of the TRS80 Color Computer series (1,2 and 3) as well as NTSC/PAL Dragon D32, D64, D200, etcetera for developmental purposes. Monetary donations help to support the hosting needs of http://www.TheLittleEngineers.org/ as well as the development and manufacture of the prototype Printed Circuit Boards.

Perhaps the easiest and most beneficial method of supporting The Little Engineers (monetarily) would be by becoming a <a href="https://www.patreon.com/TheLittleEngineers" target="_blank">Patron</a> on <a href="https://www.patreon.com/TheLittleEngineers" target="_blank">Patreon</a>. The following are among the benefits offered to <a href="https://www.patreon.com/TheLittleEngineers" target="_blank">Patrons</a>. <a href="https://www.patreon.com/TheLittleEngineers" target="_blank">Patrons</a> will receive several exclusive benefits, such as:
<p align="justify" id="patreon"><ul align="justify">
<li align="justify">FREE copies of ANY of our detailed Theory of Operation and Assembly e-books relating to our projects.
</li>
<li align="justify">Random giveaways of bare Printed Circuit Boards (PCB's) developed by The Little Engineers.
</li>
<li align="justify">Random giveaways of Kits developed by The Little Engineers.
</li>
<li align="justify">Random giveaways of assembled projects developed by The Little Engineers.
</li>
<li align="justify">The opportunity to purchase various bare Printed Circuit Boards (PCB's) developed by The Little Engineers at discounts of up to 50% off.
</li>
<li align="justify">The opportunity to purchase various Kits developed by The Little Engineers at discounts of up to 50% off.
</li>
<li align="justify">The opportunity to purchase various assembled projects developed by The Little Engineers at discounts of up to 50% off.
</li>
</ul>
<p align="justify">
We will also be publishing detailed Theory of Operation and assembly manuals for all of our open source products in e-book and paperback formats. Purchases of these e-books and/or paperbacks helps to support The Little Engineers and our continued developmental efforts. Donations may also be made in almost any variety of digital currency, including, but not limited to, the following:</p>
<p align="justify" id="digitalcurrency"><ul align="justify">
<li align="justify">BitCoin (BTC):<br>
bc1q7m3vmafshmkhz29ec8tayx3704qaa8xxhhadf5
</li>
<li align="justify">Ethereum (ETH), Ethereum Classic (ETC), Callisto (CLO) or any ETH, ETC or CLO based tokens:<br>
0xBc306a88F17cb88DaDcBB80A60E8a93E9B74558c
</li>
<li align="justify">BitCoin Cash (BCH):<br>
qr6d8mjm4fr90ryyywkhs578f0lgn7e5guue964rqz
</li>
<li align="justify">BitCoin Gold (BTG):<br>
GagaV6V46oLNzuJq1RrHzQuZXB9KvQDuv7
</li>
<li align="justify">BitCoin SV (BSV):<br>
1NVRHunKywVvkh1MgMFUQLUxEFUBxPk4vy
</li>
<li align="justify">LiteCoin (LTC):<br>
LKinnpFBxf2F8ZwTivYwLRtbX99bB9qcCE
</li>
<li align="justify">Cardano (ADA):<br>
DdzFFzCqrhsnVi7hPhGzUVeoMk2xmQvN4i4uMRUi2RED8TtsVKqj4vXY3QxEC9HbVXWrequmqemHyzEQDNcX2246tSH6jQEv1cmU7yzX
</li>
<li align="justify">Stellar Lumens (XLM):<br>
GAUVDHXFDAF36IM267NW2XOHOWAUJ7VFEXSRFBCIHHLG53IZIDXRZBX5
</li>
<li align="justify">Ripple (XRP):<br>
rp4rfoceHEdpUpp8z5r5AnS27t1JMY7j3a
</li>
<li align="justify">Binance Coin (BNB):<br>
bnb1fzyxmu2f9t5dcvccjrzjpkvye7fpgd7rwlzxfk
</li>
<li align="justify">TRON (TRX), BitTorrent (BTT), WINk (WIN), Tether USDT (TRX-USDT) or any TRX based tokens:<br>
TRx67xS64bTuoVBxE67gcirhttWuZhrVTv
</li>
<li align="justify">Multi-Collateral DAI (DAI), Compound DAI (CDAI) or Old DAI (SAI):<br>
0xBc306a88F17cb88DaDcBB80A60E8a93E9B74558c
</li>
<li align="justify">DogeCoin (DOGE):<br>
DQBceUqt9tY4SXqFNf1BWVmDjQ1hRZyzs5
</li>
<li align="justify">ARK (ARK):<br>
AXGgC9t1Xk7Pcb6cjGB2cAhfkiriNnpBP3
</li>
<li align="justify">Cosmos (ATOM):<br>
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
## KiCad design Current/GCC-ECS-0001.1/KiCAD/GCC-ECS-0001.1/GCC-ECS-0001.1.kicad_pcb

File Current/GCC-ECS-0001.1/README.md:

# 2732-tofrom-2532
This product is intended to allow a 2732 EPROM to be placed into a 2532 EPROM socket or a 2532 EPROM to be placed into a 2732 EPROM socket. The original product seems to have been placed on github at this url: https://github.com/ricardoquesada/2732-to-2532. Being involved in the original creation of the product, I decided not to fork that repository for this new, slightly improved version, but rather chose to create a new repository. The product is now licensed under a Creative Commons Attribution-ShareAlike 4.0 International (CC BY-SA 4.0) License, https://creativecommons.org/licenses/by-sa/4.0/) IN MEMORY OF MY FATHER, ROBERT EMBRY TURNER. I LOVE YOU DADDY! REST IN PEACE.

Included in the archive are design files for Eagle 5 and earlier, Eagle 6 and newer and KiCAD 5 and newer. Gerber files are also included.

2732 <--> 2532 Adapter Board: GCC-ECS-0001.1, 2532 <===> 2732 Socket Converter, Original Part Number: GCC-ECS-0001.0, Copyright (C) 04 May 2010, By: "Little" John Eric Turner and "Big" John Robert Turner, All Rights Reserved. http://www.GIMEchip.com/ Updated Part Number: GCC-ECS-0001.1, By: "Uncle" Robert "The R.A.T." Allen Turner at the behest of "Little" and "Big" John, Copyright (C) 09 April 2019, Released under a Creative Commons Attribution-ShareAlike 4.0 International (CC BY-SA 4.0) License https://creativecommons.org/licenses/by-sa/4.0/ IN MEMORY OF MY FATHER: ROBERT EMBRY TURNER. I LOVE YOU DADDY! REST IN PEACE.
 
This product is intended to allow a 2732 EPROM to be placed into a 2532 EPROM socket or a 2532 EPROM to be placed into a 2732 EPROM socket. Fitting I.C. pins for IC1 and a socket for IC2 allows a 2732 to be plugged into a 2532 socket, whilst fitting I.C. pins for IC2 and a socket for IC1 allows a 2532 to be plugged into a 2732 socket. It is recommended that "round pin headers" be used for the I.C. pins as they will plug directly into standard I.C. sockets without stressing them which would result in potential damage to the socket. A low-profile ZIF (Zero Insertion Force) socket is ideal for use as the actual socket for this device if repeated E.P.R.O.M. insertion and removal is expected. Otherwise, a low profile D.I.P. (Dual Inline Pin) socket should be used. The 2732 has an output enable signal in addition to the chip enable signal. In most cases, the output enable signal can simply be connected to ground. However, it may sometimes be desirable to connect the ouput enable signal to the chip enable signal. Jumpers JP1 and JP2 allow these settings. If JP1 is fitted, then the ouput enable will be connected to the chip enable. If JP2 is fitted, then the ouput enable will be connected to GND. JP1 and JP2 should NEVER be fitted at the same time - one or the other, but not both. In most cases, fitting JP2 will suffice.
All of GIMEchip.com's designs are created for the benefit of the vintage computing community as a whole. Although we copyright all of our works and retain all rights to them, we also don't mind sharing. If you wish to produce and distribute this product, please contact us at: sales@gimechip.com. In most* cases, permissions will be granted Royalty Free. I said we like to share, didn't I? *As of 09 April 2019, it is no longer neccessary to request permissions to use this product. This is due to the release of Version 0001.0 and the NEW Version 0001.1 under a Creative Commons Attribution-ShareAlike 4.0 International (CC BY-SA 4.0) License. This allows for almost any use, including commercial. https://creativecommons.org/licenses/by-sa/4.0/ RELEASED IN MEMORY OF MY FATHER: ROBERT EMBRY TURNER. I LOVE YOU DADDY! REST IN PEACE.

If you would like to include this product as part of your website, feel free to do so, as long as all documentation remains intact. We do ask that you inform us that you have included this file on your site so our ego's may get a bit larger :-)** Enjoy - "Little" John Eric and "Big" John Robert Turner, Son and Father. **NOTE: Due to the new licensing (CC BY-SA 4.0), it is now allowable to alter the documentation and there is no need to inform us of any website inclusion, however, attribution is still required (although we really won't complain if you forget.) THANK YOU !
The Update to Version 0001.1 was done by: Robert Allen Turner, who acquired the GIMEchip.com domain name on 25 December 2018. Please note that Robert Allen Turner is unable to answer any inquiries in relation to GIMEchip.com prior to his acquisition of same. Robert Allen Turner is in the process of releasing all prior GIMEchip.com designs under the CC BY-SA 4.0 License. This is an ambitious undertaking which is likely to require a very large amount of time.

The Little Engineers is a project began in 2011 by Robert Allen Turner (hereafter, I or Me), for the benefit of foster children and their families (foster and biological). The original intent was simply to provide a means of creating videos with the foster families such that the biological parents did not completely miss out on their children growing up. Providing simple to construct kits seemed a logical choice as a subject for such videos and that is primarily what I attempt to develop for use in such videos. This also makes the process educational. This is a difficult undertaking, as each case must be handled on an individual basis and any such videos and communications must be scrutinized and approved on a per case basis by the case workers, et alia in charge. Although this makes such an undertaking extremely difficult, it is a neccessity in order to protect the children. Some are, after all, being protected from abusive family members and so on. So there has to be a very strict set of protocols in place. This has prevented me from fully launching The Little Engineers over the past eight years, but I remain commited to the project.

The logos, names and other material relating to The Little Engineers, TheLittleEngineers.org and GIMEchip.com are the sole property of Robert Allen Turner with All Rights Reserved. The rights to the GIMEchip.com domain and products were acquired by the author on 25 December 2018. Merry Happy Christmas! Please note that the author is unable to answer any inquiries, including those of support or otherwise, in relation to GIMEchip.com prior to his acquisition of same on 25 December 2018.
http://www.TheLittleEngineers.org

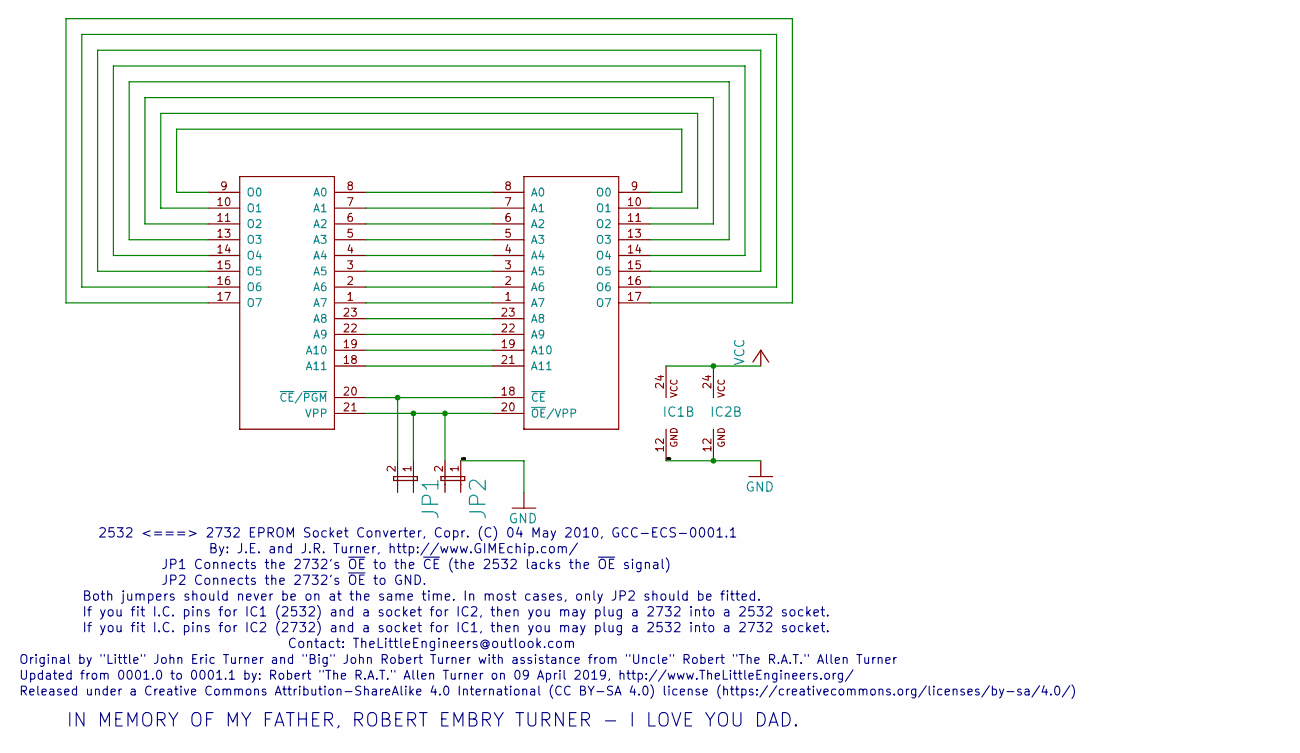
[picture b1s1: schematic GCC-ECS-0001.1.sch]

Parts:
IC1: 2532; DIL24
IC2: 2732; DIL24
JP1, JP2: JP; JP1

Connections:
GND: IC1.12 (GND), IC2.12 (GND), JP2.1
unnamed: IC1.1 (A7), IC2.1 (A7)
unnamed: IC1.2 (A6), IC2.2 (A6)
unnamed: IC1.3 (A5), IC2.3 (A5)
unnamed: IC1.4 (A4), IC2.4 (A4)
unnamed: IC1.5 (A3), IC2.5 (A3)
unnamed: IC1.6 (A2), IC2.6 (A2)
unnamed: IC1.7 (A1), IC2.7 (A1)
unnamed: IC1.8 (A0), IC2.8 (A0)
unnamed: IC1.9 (O0), IC2.9 (O0)
unnamed: IC1.10 (O1), IC2.10 (O1)
unnamed: IC1.11 (O2), IC2.11 (O2)
unnamed: IC1.13 (O3), IC2.13 (O3)
unnamed: IC1.14 (O4), IC2.14 (O4)
unnamed: IC1.15 (O5), IC2.15 (O5)
unnamed: IC1.16 (O6), IC2.16 (O6)
unnamed: IC1.17 (O7), IC2.17 (O7)
unnamed: IC1.18 (A11), IC2.21 (A11)
unnamed: IC1.19 (A10), IC2.19 (A10)
unnamed: IC1.20 (~CE~/~PGM), IC2.18 (~CE), JP1.2
unnamed: IC1.21 (VPP), IC2.20 (~OE~/VPP), JP1.1, JP2.2
unnamed: IC1.22 (A9), IC2.22 (A9)
unnamed: IC1.23 (A8), IC2.23 (A8)
VCC: IC1.24 (VCC), IC2.24 (VCC)

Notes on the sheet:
2532 <===> 2732 EPROM Socket Converter, Copr. (C) 04 May 2010, GCC-ECS-0001.1
By: J.E. and J.R. Turner, http://www.GIMEchip.com/
JP1 Connects the 2732's ~OE~ to the ~CE~ (the 2532 lacks the ~OE~ signal)
JP2 Connects the 2732's ~OE~ to GND.
Both jumpers should never be on at the same time. In most cases, only JP2 should be fitted.
Contact: TheLittleEngineers@outlook.com
If you fit I.C. pins for IC1 (2532) and a socket for IC2, then you may plug a 2732 into a 2532 socket.
If you fit I.C. pins for IC2 (2732) and a socket for IC1, then you may plug a 2532 into a 2732 socket.
Original by "Little" John Eric Turner and "Big" John Robert Turner with assistance from "Uncle" Robert "The R.A.T." Allen Turner
Updated from 0001.0 to 0001.1 by: Robert "The R.A.T." Allen Turner on 09 April 2019, http://www.TheLittleEngineers.org/
Released under a Creative Commons Attribution-ShareAlike 4.0 International (CC BY-SA 4.0) license (https://creativecommons.org/licenses/by-sa/4.0/)
IN MEMORY OF MY FATHER, ROBERT EMBRY TURNER - I LOVE YOU DAD.

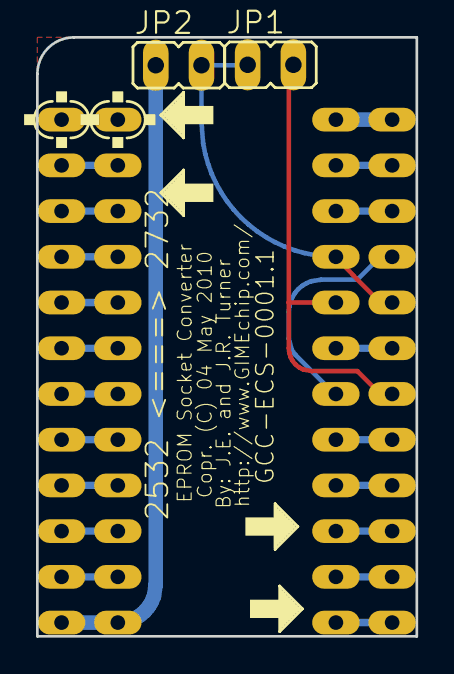
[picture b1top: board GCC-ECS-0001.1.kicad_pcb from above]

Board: 16 copper layers, 21.1 x 33.3 mm, 9 parts (0 on the bottom side), 24 nets.

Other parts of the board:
U$1, U$2: ARROW-L
U$3, U$4: ARROW-R
U$5: TLE-LOGO

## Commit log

2019-07-31 Added DIRectories for better organization
2019-08-01 Maintenance

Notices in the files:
README.md:
All products developed by The Little Engineers are completely free to use under the terms of the Creative Commons Attribution-ShareAlike 4.0 International (CC BY-SA 4.0) License, even for commercial purposes.
parts and their libraries:
Unless otherwise noted, content of this library is licensed under a Creative Commons Attribution-ShareAlike 4.0 International (CC BY-SA 4.0) license (https://creativecommons.org/licenses/by-sa/4.0/)
©2019 Robert Allen Turner, ALL RIGHTS RESERVED.
